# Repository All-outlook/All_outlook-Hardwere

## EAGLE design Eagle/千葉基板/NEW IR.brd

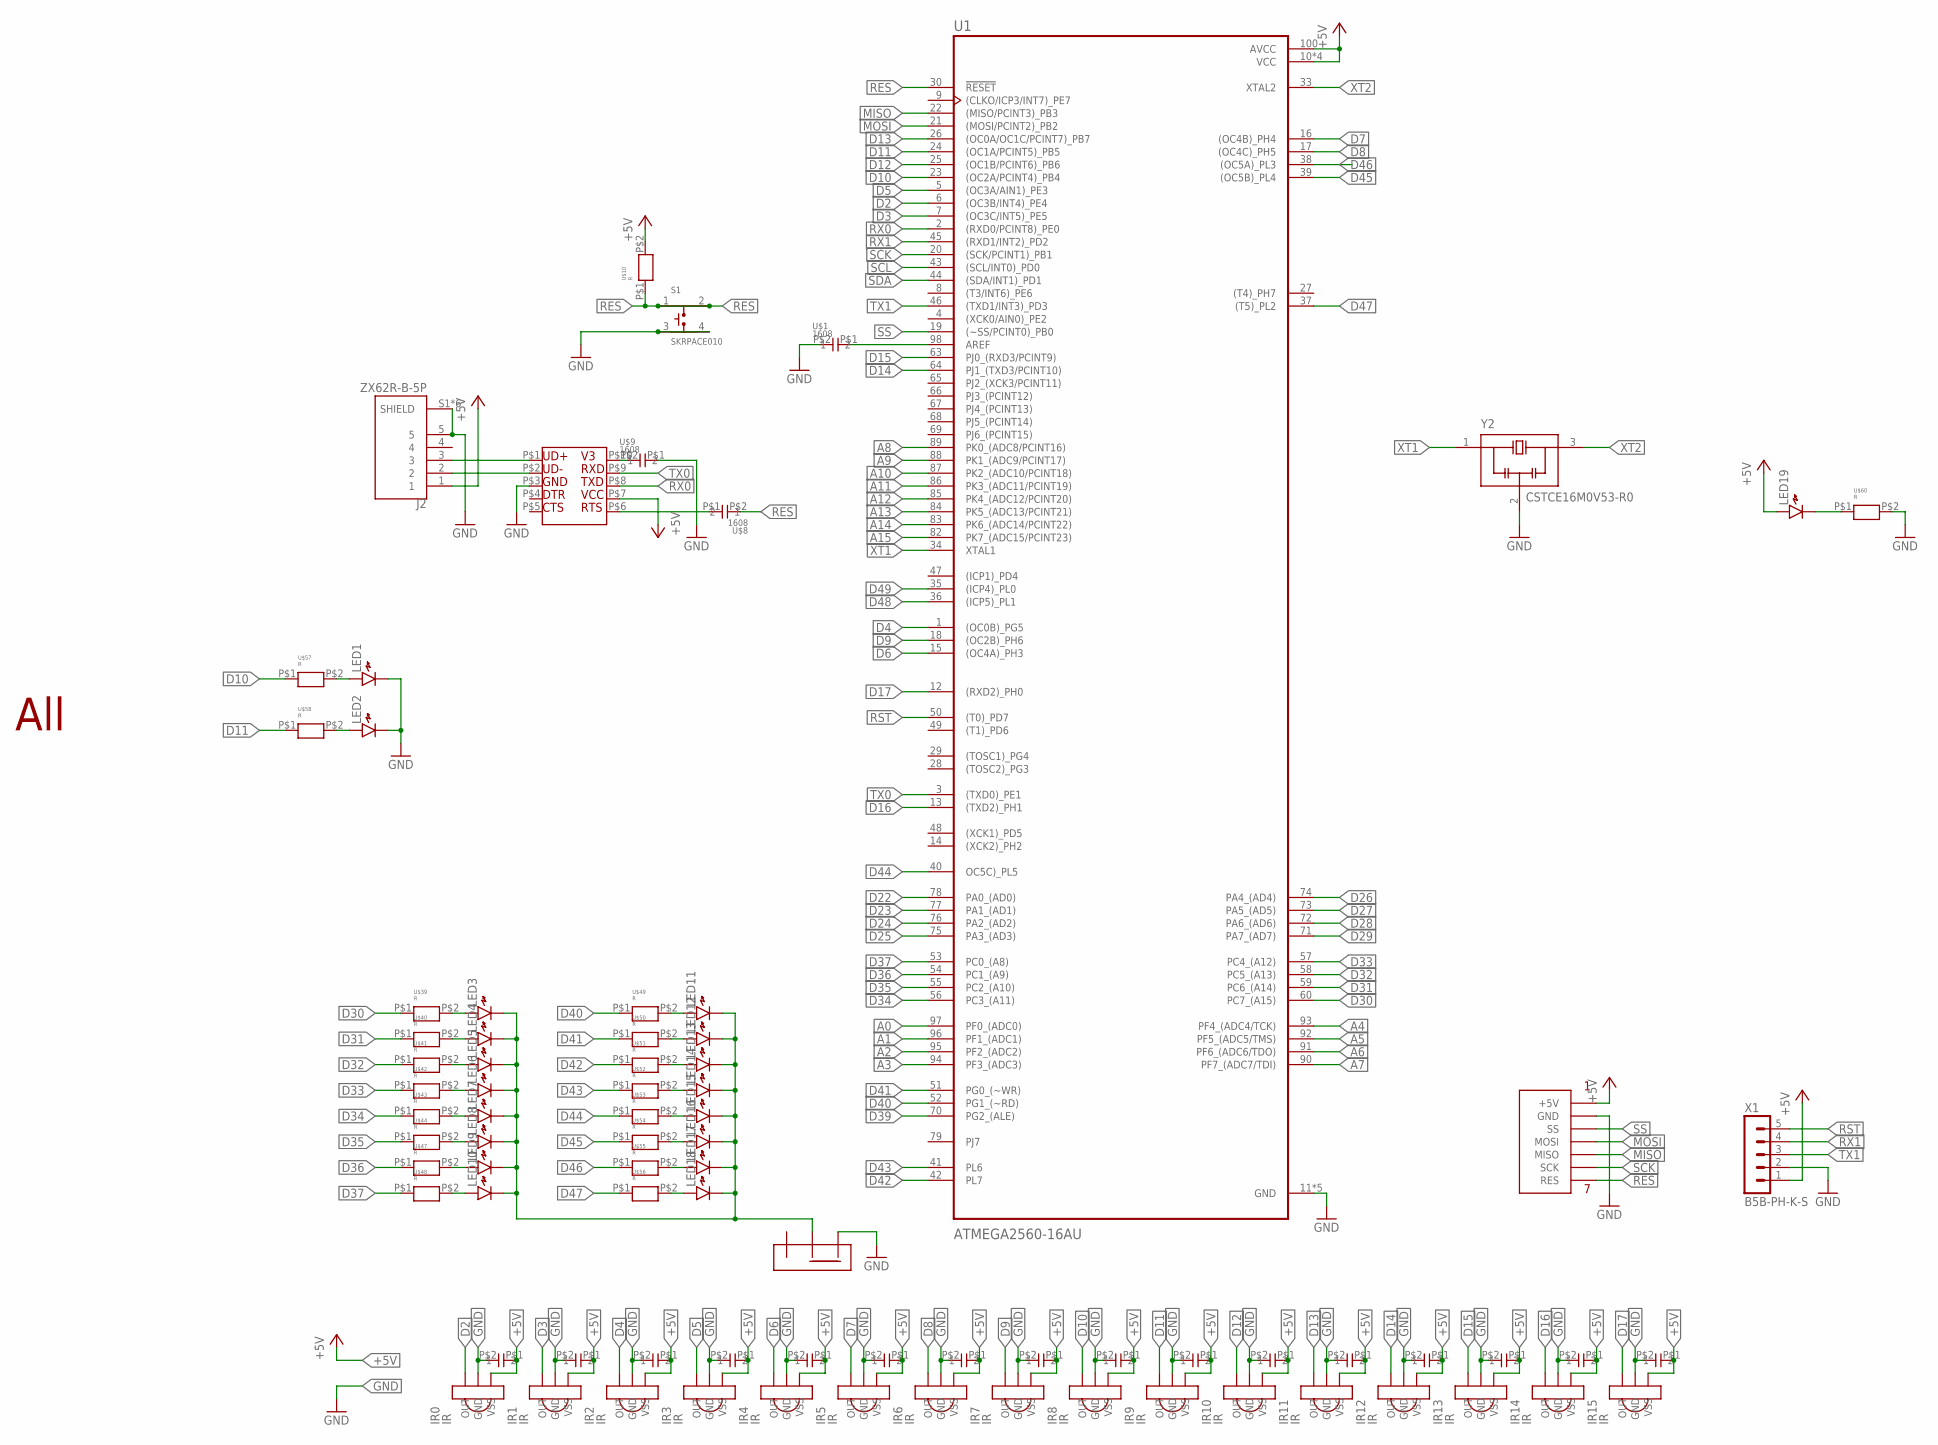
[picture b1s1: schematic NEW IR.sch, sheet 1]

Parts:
IR0, IR1, IR2, IR3, IR4, IR5, IR6, IR7, IR8, IR9, IR10, IR11, IR12, IR13, IR14, IR15: IR
J2: ZX62R-B-5P; HRS_ZX62R-B-5P
LED1, LED2, LED3, LED4, LED5, LED6, LED7, LED8, LED9, LED10, LED11, LED12, LED13, LED14, LED15, LED16, LED17, LED18, LED19: LED1608
S1: SKRPACE010; SW_SKRPACE010
U1: ATMEGA2560-16AU; QFP50P1600X1600X120-100N
U$1, U$2, U$4, U$6, U$8, U$9, U$14, U$16, U$18, U$20, U$22, U$24, U$26, U$28, U$30, U$32, U$34, U$36, U$38: 1608; CON
U$3: ALL
U$5: SSW
U$7: CH340K
U$10, U$39, U$40, U$41, U$42, U$43, U$44, U$47, U$48, U$49, U$50, U$51, U$52, U$53, U$54, U$55, U$56, U$57, U$58, U$60: R; 1608
U$59: SPI
X1: B5B-PH-K-S
Y2: CSTCE16M0V53-R0; OSC_CSTCE16M0V53-R0

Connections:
+5V: IR0.P$3 (VSS), IR1.P$3 (VSS), IR2.P$3 (VSS), IR3.P$3 (VSS), IR4.P$3 (VSS), IR5.P$3 (VSS), IR6.P$3 (VSS), IR7.P$3 (VSS), IR8.P$3 (VSS), IR9.P$3 (VSS), IR10.P$3 (VSS), IR11.P$3 (VSS), IR12.P$3 (VSS), IR13.P$3 (VSS), IR14.P$3 (VSS), IR15.P$3 (VSS), J2.1, LED19.A, U1.10 (VCC), U1.31 (VCC), U1.61 (VCC), U1.80 (VCC), U1.100 (AVCC), U$2.P$1 (1), U$4.P$1 (1), U$6.P$1 (1), U$7.P$7, U$10.P$2, U$14.P$1 (1), U$16.P$1 (1), U$18.P$1 (1), U$20.P$1 (1), U$22.P$1 (1), U$24.P$1 (1), U$26.P$1 (1), U$28.P$1 (1), U$30.P$1 (1), U$32.P$1 (1), U$34.P$1 (1), U$36.P$1 (1), U$38.P$1 (1), U$59.P$1 (+5V), X1.1
A0: U1.97 (PF0_(ADC0))
A1: U1.96 (PF1_(ADC1))
A2: U1.95 (PF2_(ADC2))
A3: U1.94 (PF3_(ADC3))
A4: U1.93 (PF4_(ADC4/TCK))
A5: U1.92 (PF5_(ADC5/TMS))
A6: U1.91 (PF6_(ADC6/TDO))
A7: U1.90 (PF7_(ADC7/TDI))
A8: U1.89 (PK0_(ADC8/PCINT16))
A9: U1.88 (PK1_(ADC9/PCINT17))
A10: U1.87 (PK2_(ADC10/PCINT18))
A11: U1.86 (PK3_(ADC11/PCINT19))
A12: U1.85 (PK4_(ADC12/PCINT20))
A13: U1.84 (PK5_(ADC13/PCINT21))
A14: U1.83 (PK6_(ADC14/PCINT22))
A15: U1.82 (PK7_(ADC15/PCINT23))
D2: IR0.P$1 (OUT), U1.6 ((OC3B/INT4)_PE4)
D3: IR1.P$1 (OUT), U1.7 ((OC3C/INT5)_PE5)
D4: IR2.P$1 (OUT), U1.1 ((OC0B)_PG5)
D5: IR3.P$1 (OUT), U1.5 ((OC3A/AIN1)_PE3)
D6: IR4.P$1 (OUT), U1.15 ((OC4A)_PH3)
D7: IR5.P$1 (OUT), U1.16 ((OC4B)_PH4)
D8: IR6.P$1 (OUT), U1.17 ((OC4C)_PH5)
D9: IR7.P$1 (OUT), U1.18 ((OC2B)_PH6)
D10: IR8.P$1 (OUT), U1.23 ((OC2A/PCINT4)_PB4), U$57.P$1
D11: IR9.P$1 (OUT), U1.24 ((OC1A/PCINT5)_PB5), U$58.P$1
D12: IR10.P$1 (OUT), U1.25 ((OC1B/PCINT6)_PB6)
D13: IR11.P$1 (OUT), U1.26 ((OC0A/OC1C/PCINT7)_PB7)
D14: IR12.P$1 (OUT), U1.64 (PJ1_(TXD3/PCINT10))
D15: IR13.P$1 (OUT), U1.63 (PJ0_(RXD3/PCINT9))
D16: IR14.P$1 (OUT), U1.13 ((TXD2)_PH1)
D17: IR15.P$1 (OUT), U1.12 ((RXD2)_PH0)
D22: U1.78 (PA0_(AD0))
D23: U1.77 (PA1_(AD1))
D24: U1.76 (PA2_(AD2))
D25: U1.75 (PA3_(AD3))
D26: U1.74 (PA4_(AD4))
D27: U1.73 (PA5_(AD5))
D28: U1.72 (PA6_(AD6))
D29: U1.71 (PA7_(AD7))
D30: U1.60 (PC7_(A15)), U$39.P$1
D31: U1.59 (PC6_(A14)), U$40.P$1
D32: U1.58 (PC5_(A13)), U$41.P$1
D33: U1.57 (PC4_(A12)), U$42.P$1
D34: U1.56 (PC3_(A11)), U$43.P$1
D35: U1.55 (PC2_(A10)), U$44.P$1
D36: U1.54 (PC1_(A9)), U$47.P$1
D37: U1.53 (PC0_(A8)), U$48.P$1
D39: U1.70 (PG2_(ALE))
D40: U1.52 (PG1_(~RD)), U$49.P$1
D41: U1.51 (PG0_(~WR)), U$50.P$1
D42: U1.42 (PL7), U$51.P$1
D43: U1.41 (PL6), U$52.P$1
D44: U1.40 (OC5C)_PL5), U$53.P$1
D45: U1.39 ((OC5B)_PL4), U$54.P$1
D46: U1.38 ((OC5A)_PL3), U$55.P$1
D47: U1.37 ((T5)_PL2), U$56.P$1
D48: U1.36 ((ICP5)_PL1)
D49: U1.35 ((ICP4)_PL0)
GND: IR0.P$2 (GND), IR1.P$2 (GND), IR2.P$2 (GND), IR3.P$2 (GND), IR4.P$2 (GND), IR5.P$2 (GND), IR6.P$2 (GND), IR7.P$2 (GND), IR8.P$2 (GND), IR9.P$2 (GND), IR10.P$2 (GND), IR11.P$2 (GND), IR12.P$2 (GND), IR13.P$2 (GND), IR14.P$2 (GND), IR15.P$2 (GND), J2.5, J2.S1 (SHIELD), J2.S2 (SHIELD), J2.S3 (SHIELD), J2.S4 (SHIELD), J2.S5 (SHIELD), J2.S6 (SHIELD), LED1.K, LED2.K, S1.3, S1.4, U1.11 (GND), U1.32 (GND), U1.62 (GND), U1.81 (GND), U1.99 (GND), U$1.P$2 (2), U$2.P$2 (2), U$4.P$2 (2), U$5.P$1, U$6.P$2 (2), U$7.P$3, U$9.P$1 (1), U$14.P$2 (2), U$16.P$2 (2), U$18.P$2 (2), U$20.P$2 (2), U$22.P$2 (2), U$24.P$2 (2), U$26.P$2 (2), U$28.P$2 (2), U$30.P$2 (2), U$32.P$2 (2), U$34.P$2 (2), U$36.P$2 (2), U$38.P$2 (2), U$59.P$2 (GND), U$60.P$2, X1.2, Y2.2 (GND)
MISO: U1.22 ((MISO/PCINT3)_PB3), U$59.P$5 (MISO)
MOSI: U1.21 ((MOSI/PCINT2)_PB2), U$59.P$4 (MOSI)
unnamed: LED3.A, U$39.P$2
unnamed: LED4.A, U$40.P$2
unnamed: LED5.A, U$41.P$2
unnamed: LED6.A, U$42.P$2
unnamed: LED7.A, U$43.P$2
unnamed: LED8.A, U$44.P$2
unnamed: LED9.A, U$47.P$2
unnamed: LED2.A, U$58.P$2
unnamed: LED1.A, U$57.P$2
unnamed: LED3.K, LED4.K, LED5.K, LED6.K, LED7.K, LED8.K, LED9.K, LED10.K, LED11.K, LED12.K, LED13.K, LED14.K, LED15.K, LED16.K, LED17.K, LED18.K, U$5.P$3
unnamed: U$7.P$6, U$8.P$1 (1)
unnamed: J2.2, U$7.P$2
unnamed: J2.3, U$7.P$1
unnamed: U$7.P$10, U$9.P$2 (2)
unnamed: LED10.A, U$48.P$2
unnamed: LED11.A, U$49.P$2
unnamed: LED12.A, U$50.P$2
unnamed: LED13.A, U$51.P$2
unnamed: LED14.A, U$52.P$2
unnamed: LED15.A, U$53.P$2
unnamed: LED16.A, U$54.P$2
unnamed: LED17.A, U$55.P$2
unnamed: LED18.A, U$56.P$2
unnamed: LED19.K, U$60.P$1
unnamed: U1.98 (AREF), U$1.P$1 (1)
RES: S1.1, S1.2, U1.30 (!RESET), U$8.P$2 (2), U$10.P$1, U$59.P$7 (RES)
RST: U1.50 ((T0)_PD7), X1.5
RX0: U1.2 ((RXD0/PCINT8)_PE0), U$7.P$8
RX1: U1.45 ((RXD1/INT2)_PD2), X1.4
SCK: U1.20 ((SCK/PCINT1)_PB1), U$59.P$6 (SCK)
SCL: U1.43 ((SCL/INT0)_PD0)
SDA: U1.44 ((SDA/INT1)_PD1)
SS: U1.19 ((~SS/PCINT0)_PB0), U$59.P$3 (SS)
TX0: U1.3 ((TXD0)_PE1), U$7.P$9
TX1: U1.46 ((TXD1/INT3)_PD3), X1.3
XT1: U1.34 (XTAL1), Y2.1 (IN)
XT2: U1.33 (XTAL2), Y2.3 (OUT)

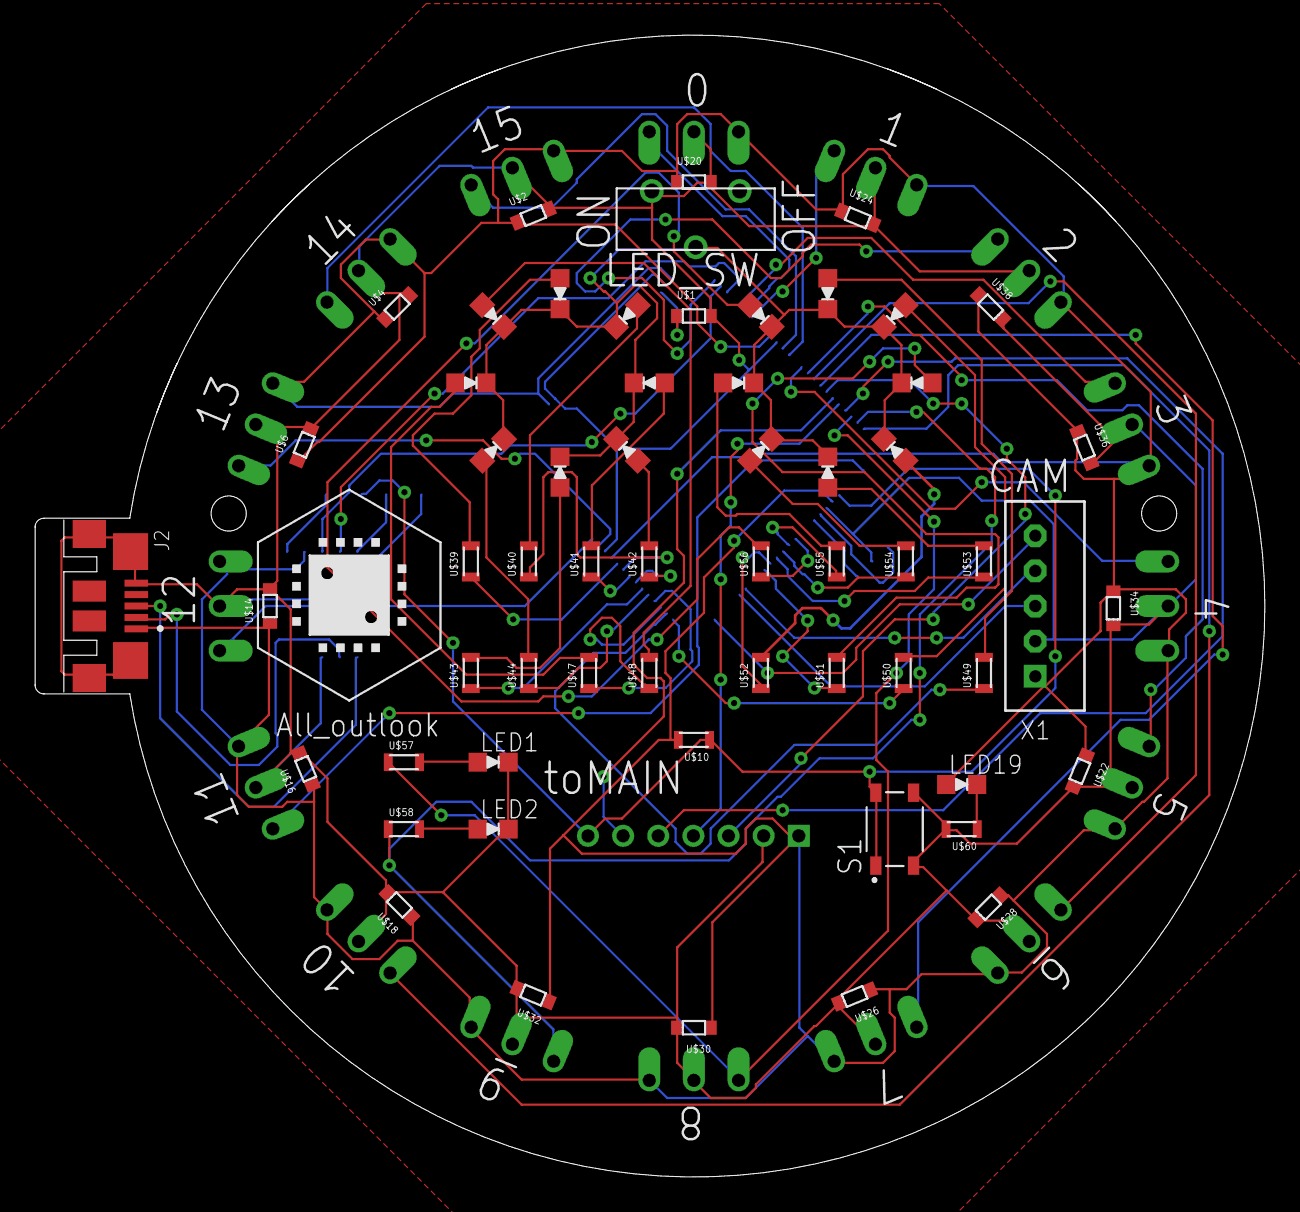
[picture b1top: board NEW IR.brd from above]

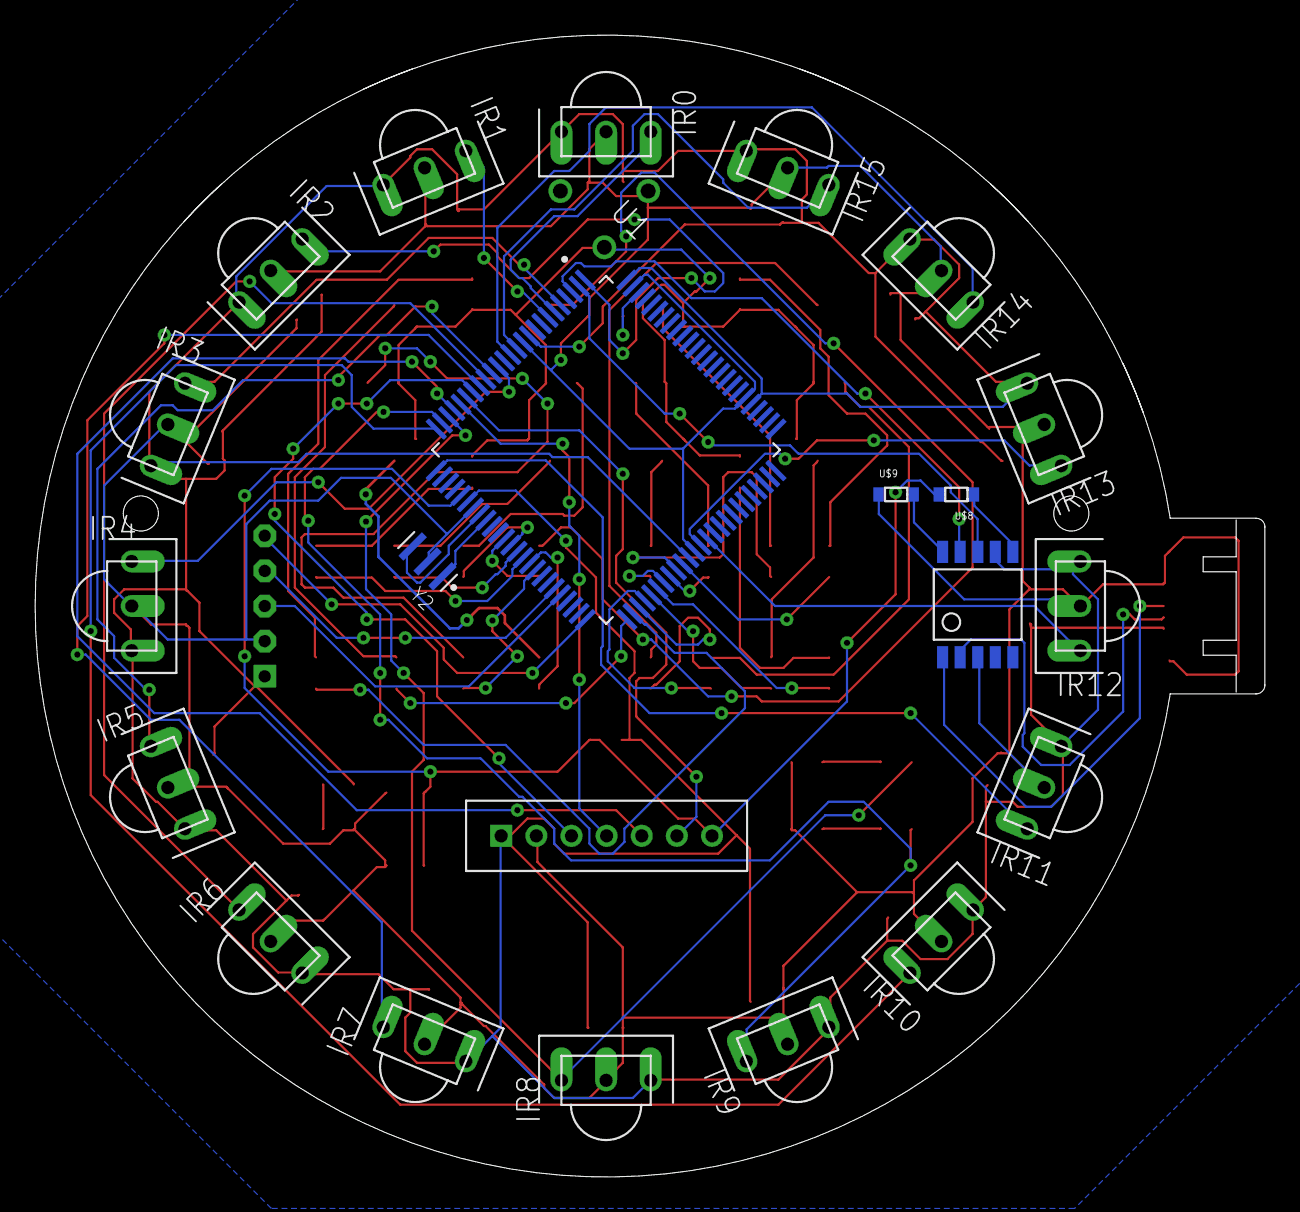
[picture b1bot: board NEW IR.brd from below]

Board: 2 copper layers, 70.0 x 65.0 mm, 83 parts (22 on the bottom side), 71 nets.

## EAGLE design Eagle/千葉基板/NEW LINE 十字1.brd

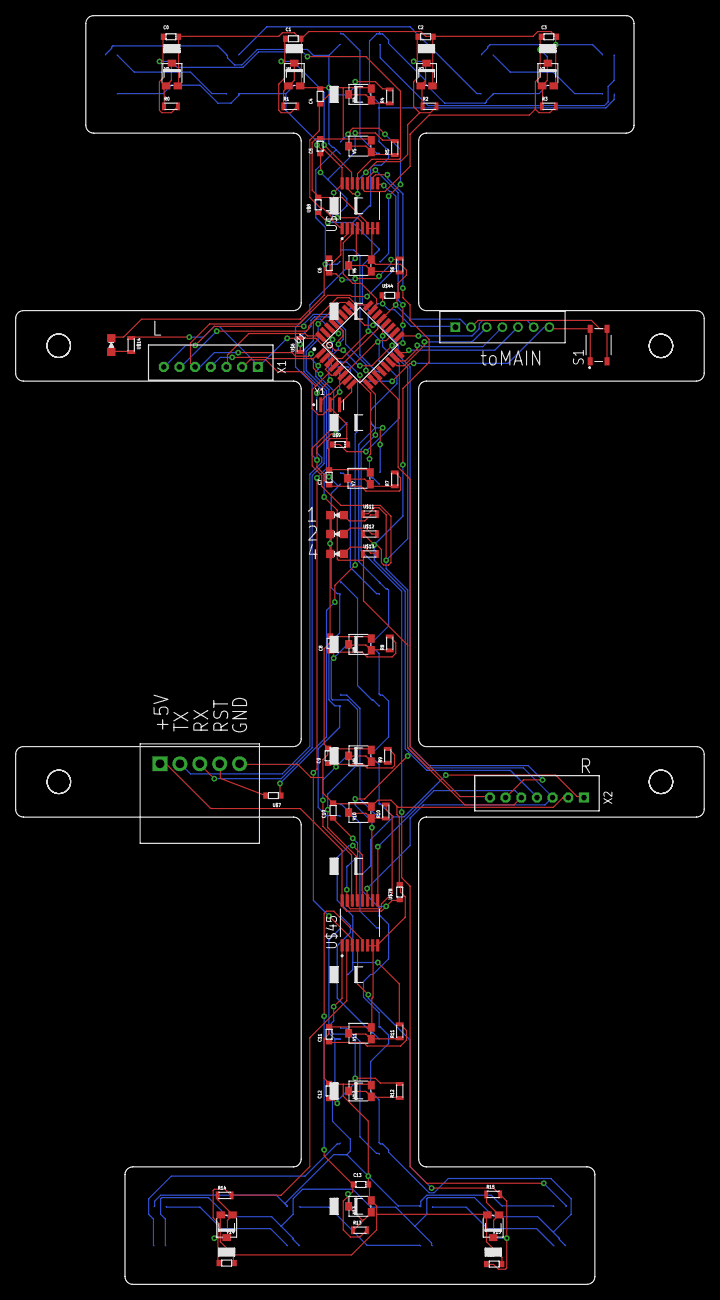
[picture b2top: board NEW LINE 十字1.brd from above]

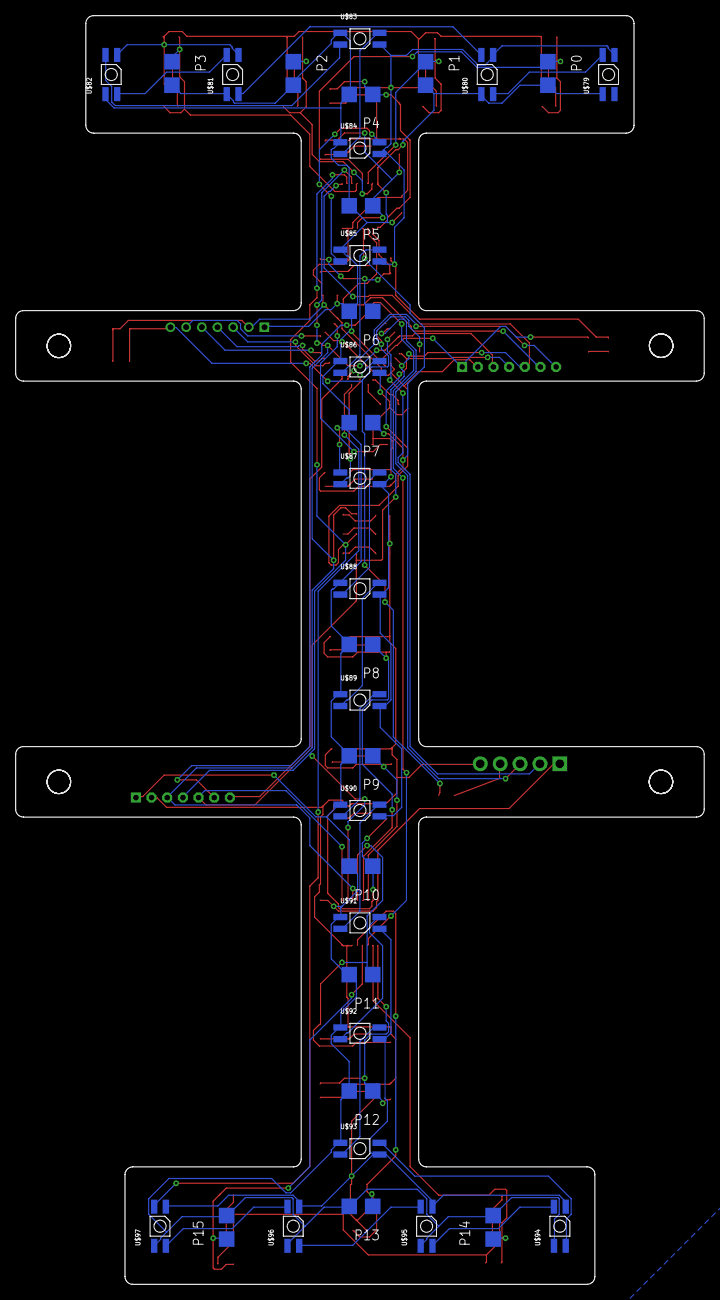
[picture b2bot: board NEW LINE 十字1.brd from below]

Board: 2 copper layers, 87.9 x 162.0 mm, 106 parts (19 on the bottom side), 77 nets.

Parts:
C0, C1, C2, C3, C4, C5, C6, C7, C8, C9, C10, C11, C12, C13, C14, C15: 1608; CON
LED5, LED6, LED7, LED8: LED1608
P0, P1, P2, P3, P4, P5, P6, P7, P8, P9, P10, P11, P12, P13, P14, P15: PHOTO
R0, R1, R2, R3, R4, R5, R6, R7, R8, R9, R10, R11, R12, R13, R14, R15: R; 1608
S1: SKRPACE010; SW_SKRPACE010
U1: ATMEGA328P-AU; QFP80P900X900X120-32N
U$1, U$45: AM; SOP65P640X120-16N
U$6, U$11, U$12, U$13, U$14: R; 1608
U$7, U$8, U$9, U$44, U$78: 1608; CON
U$10: SI
U$15: SPI
U$79, U$80, U$81, U$82, U$83, U$84, U$85, U$86, U$87, U$88, U$89, U$90, U$91, U$92, U$93, U$94, U$95, U$96, U$97: LED
V0, V1, V2, V3, V4, V5, V6, V7, V8, V9, V10, V11, V12, V13, V14, V15: VR
X1, X2: B7B-PH-K-S
Y1: CSTCE16M0V53-R0; OSC_CSTCE16M0V53-R0

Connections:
+5V: P0.P$1, P1.P$1, P2.P$1, P3.P$1, P4.P$1, P5.P$1, P6.P$1, P7.P$1, P8.P$1, P9.P$1, P10.P$1, P11.P$1, P12.P$1, P13.P$1, P14.P$1, P15.P$1, U1.4, U1.6, U1.18, U$1.16, U$6.P$2, U$8.P$1, U$10.P$1, U$14.P$1, U$15.P$1, U$44.P$1, U$45.16, U$78.P$1, U$79.P$1, U$80.P$1, U$81.P$1, U$82.P$1, U$83.P$1, U$84.P$1, U$85.P$1, U$86.P$1, U$87.P$1, U$88.P$1, U$89.P$1, U$90.P$1, U$91.P$1, U$92.P$1, U$93.P$1, U$94.P$1, U$95.P$1, U$96.P$1, U$97.P$1, X1.1, X2.1
A0: U1.23, U$1.3
A1: U1.24, X1.6
A2: U1.25, U$45.3
A3: U1.26, X2.6
CH0: C0.P$1, P0.P$2, R0.P$2, U$1.13
CH1: C1.P$1, P1.P$2, R1.P$2, U$1.14
CH2: C2.P$1, P2.P$2, R2.P$2, U$1.15
CH3: C3.P$1, P3.P$2, R3.P$2, U$1.12
CH4: C4.P$1, P4.P$2, R4.P$2, U$1.1
CH5: C5.P$1, P5.P$2, R5.P$2, U$1.5
CH6: C6.P$1, P6.P$2, R6.P$2, U$1.2
CH7: C7.P$1, P7.P$2, R7.P$2, U$1.4
CH8: C8.P$1, P8.P$2, R8.P$2, U$45.13
CH9: C9.P$1, P9.P$2, R9.P$2, U$45.14
CH10: C10.P$1, P10.P$2, R10.P$2, U$45.15
CH11: C11.P$1, P11.P$2, R11.P$2, U$45.12
CH12: C12.P$1, P12.P$2, R12.P$2, U$45.1
CH13: C13.P$1, P13.P$2, R13.P$2, U$45.5
CH14: C14.P$1, P14.P$2, R14.P$2, U$45.2
CH15: C15.P$1, P15.P$2, R15.P$2, U$45.4
D2: U1.32, U$1.11, U$11.P$1, U$45.11, X1.3, X2.3
D3: U1.1, U$1.10, U$12.P$1, U$45.10, X1.4, X2.4
D4: U1.2, U$1.9, U$13.P$1, U$45.9, X1.5, X2.5
D5: U1.9, U$97.P$4
D6: U1.10, X1.7
D7: U1.11, X2.7
GND: C0.P$2, C1.P$2, C2.P$2, C3.P$2, C4.P$2, C5.P$2, C6.P$2, C7.P$2, C8.P$2, C9.P$2, C10.P$2, C11.P$2, C12.P$2, C13.P$2, C14.P$2, C15.P$2, LED5.K, LED6.K, LED7.K, LED8.K, S1.3, S1.4, U1.3, U1.5, U1.21, U$1.6, U$1.7, U$1.8, U$8.P$2, U$9.P$2, U$10.P$5, U$15.P$2, U$44.P$2, U$45.6, U$45.7, U$45.8, U$78.P$2, U$79.P$3, U$80.P$3, U$81.P$3, U$82.P$3, U$83.P$3, U$84.P$3, U$85.P$3, U$86.P$3, U$87.P$3, U$88.P$3, U$89.P$3, U$90.P$3, U$91.P$3, U$92.P$3, U$93.P$3, U$94.P$3, U$95.P$3, U$96.P$3, U$97.P$3, V0.P$3, V1.P$3, V2.P$3, V3.P$3, V4.P$3, V5.P$3, V6.P$3, V7.P$3, V8.P$3, V9.P$3, V10.P$3, V11.P$3, V12.P$3, V13.P$3, V14.P$3, V15.P$3, X1.2, X2.2, Y1.2
MISO: U1.16, U$15.P$5
MOSI: U1.15, U$15.P$4
unnamed: R0.P$1, V0.P$1, V0.P$2
unnamed: R1.P$1, V1.P$1, V1.P$2
unnamed: R2.P$1, V2.P$1, V2.P$2
unnamed: U1.20, U$9.P$1
unnamed: U$7.P$2, U$10.P$4
unnamed: U1.31, U$10.P$2
unnamed: U1.30, U$10.P$3
unnamed: U1.7, Y1.1
unnamed: U1.8, Y1.3
unnamed: LED7.A, U$13.P$2
unnamed: LED6.A, U$12.P$2
unnamed: LED5.A, U$11.P$2
unnamed: LED8.A, U$14.P$2
unnamed: R3.P$1, V3.P$1, V3.P$2
unnamed: R4.P$1, V4.P$1, V4.P$2
unnamed: R5.P$1, V5.P$1, V5.P$2
unnamed: R6.P$1, V6.P$1, V6.P$2
unnamed: R7.P$1, V7.P$1, V7.P$2
unnamed: R8.P$1, V8.P$1, V8.P$2
unnamed: R9.P$1, V9.P$1, V9.P$2
unnamed: R10.P$1, V10.P$1, V10.P$2
unnamed: R11.P$1, V11.P$1, V11.P$2
unnamed: R12.P$1, V12.P$1, V12.P$2
unnamed: R13.P$1, V13.P$1, V13.P$2
unnamed: R14.P$1, V14.P$1, V14.P$2
unnamed: R15.P$1, V15.P$1, V15.P$2
unnamed: U$79.P$4, U$80.P$2
unnamed: U$80.P$4, U$81.P$2
unnamed: U$81.P$4, U$82.P$2
unnamed: U$82.P$4, U$83.P$2
unnamed: U$83.P$4, U$84.P$2
unnamed: U$84.P$4, U$85.P$2
unnamed: U$85.P$4, U$86.P$2
unnamed: U$86.P$4, U$87.P$2
unnamed: U$87.P$4, U$88.P$2
unnamed: U$88.P$4, U$89.P$2
unnamed: U$89.P$4, U$90.P$2
unnamed: U$90.P$4, U$91.P$2
unnamed: U$91.P$4, U$92.P$2
unnamed: U$92.P$4, U$93.P$2
unnamed: U$93.P$4, U$94.P$2
unnamed: U$94.P$4, U$95.P$2
unnamed: U$95.P$4, U$96.P$2
unnamed: U$96.P$4, U$97.P$2
RES: S1.1, S1.2, U1.29, U$6.P$1, U$7.P$1, U$15.P$7
SCK: U1.17, U$15.P$6
SS: U1.14, U$15.P$3

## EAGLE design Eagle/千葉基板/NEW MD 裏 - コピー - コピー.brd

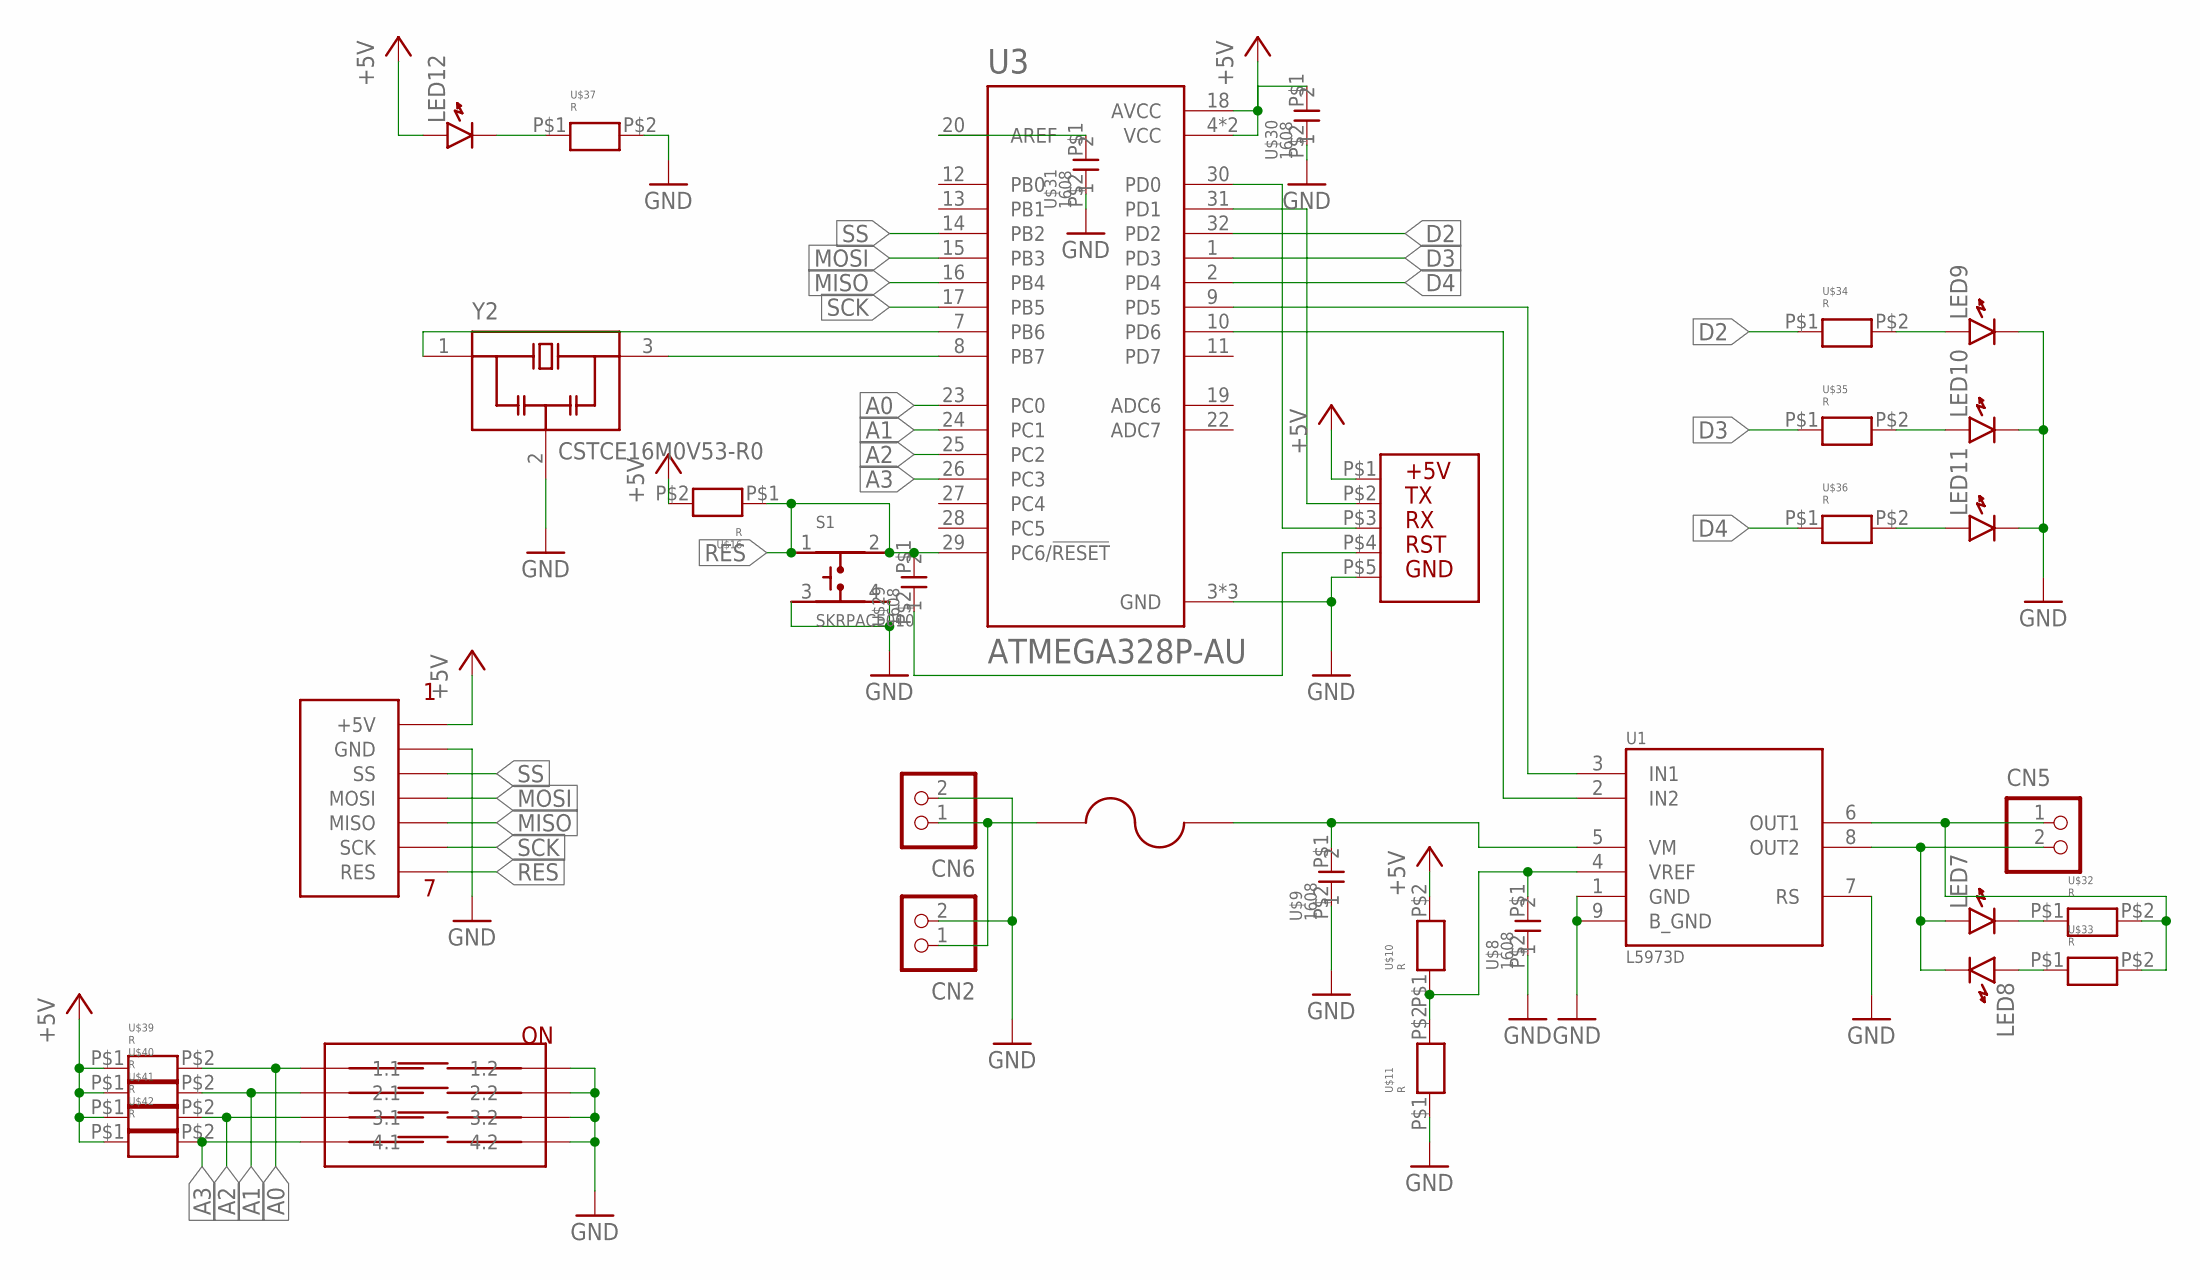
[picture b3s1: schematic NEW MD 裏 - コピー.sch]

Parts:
CN2, CN6: B2B-XH-A
CN5: S2B-XH-A
LED7, LED8, LED9, LED10, LED11, LED12: LED1608
S1: SKRPACE010; SW_SKRPACE010
U1: L5973D; SOIC127P600X170-9N
U3: ATMEGA328P-AU; QFP80P900X900X120-32N
U$1: FUSE3.7A
U$8, U$9, U$29, U$30, U$31: 1608; CON
U$10, U$11, U$16, U$32, U$33, U$34, U$35, U$36, U$37, U$39, U$40, U$41, U$42: R; 1608
U$38: 4P
U$43: SPI
U$44: SI
Y2: CSTCE16M0V53-R0; OSC_CSTCE16M0V53-R0

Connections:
+5V: LED12.A, U3.4 (VCC), U3.6 (VCC), U3.18 (AVCC), U$10.P$2, U$16.P$2, U$30.P$1 (1), U$39.P$1, U$40.P$1, U$41.P$1, U$42.P$1, U$43.P$1 (+5V), U$44.P$1
A0: U3.23 (PC0), U$38.1.1, U$39.P$2
A1: U3.24 (PC1), U$38.2.1, U$40.P$2
A2: U3.25 (PC2), U$38.3.1, U$41.P$2
A3: U3.26 (PC3), U$38.4.1, U$42.P$2
D2: U3.32 (PD2), U$34.P$1
D3: U3.1 (PD3), U$35.P$1
D4: U3.2 (PD4), U$36.P$1
GND: CN2.2, CN6.2, LED9.K, LED10.K, LED11.K, S1.3, S1.4, U1.1 (GND), U1.7 (RS), U1.9 (B_GND), U3.3 (GND), U3.5 (GND), U3.21 (GND), U$8.P$2 (2), U$9.P$2 (2), U$11.P$1, U$30.P$2 (2), U$31.P$2 (2), U$37.P$2, U$38.1.2, U$38.2.2, U$38.3.2, U$38.4.2, U$43.P$2 (GND), U$44.P$5, Y2.2 (GND)
MISO: U3.16 (PB4), U$43.P$5 (MISO)
MOSI: U3.15 (PB3), U$43.P$4 (MOSI)
unnamed: U1.5 (VM), U$1.P$2, U$9.P$1 (1)
unnamed: U1.4 (VREF), U$8.P$1 (1), U$10.P$1, U$11.P$2
unnamed: U3.20 (AREF), U$31.P$1 (1)
unnamed: U$29.P$2 (2), U$44.P$4
unnamed: U3.31 (PD1), U$44.P$2
unnamed: U3.30 (PD0), U$44.P$3
unnamed: CN2.1, CN6.1, U$1.P$1
unnamed: CN5.2, LED7.A, LED8.K, U1.8 (OUT2)
unnamed: CN5.1, U1.6 (OUT1), U$32.P$2, U$33.P$2
unnamed: U1.2 (IN2), U3.10 (PD6)
unnamed: U1.3 (IN1), U3.9 (PD5)
unnamed: U3.7 (PB6), Y2.1 (IN)
unnamed: U3.8 (PB7), Y2.3 (OUT)
unnamed: LED8.A, U$33.P$1
unnamed: LED7.K, U$32.P$1
unnamed: LED10.A, U$35.P$2
unnamed: LED9.A, U$34.P$2
unnamed: LED11.A, U$36.P$2
unnamed: LED12.K, U$37.P$1
RES: S1.1, S1.2, U3.29 (PC6/!RESET), U$16.P$1, U$29.P$1 (1), U$43.P$7 (RES)
SCK: U3.17 (PB5), U$43.P$6 (SCK)
SS: U3.14 (PB2), U$43.P$3 (SS)

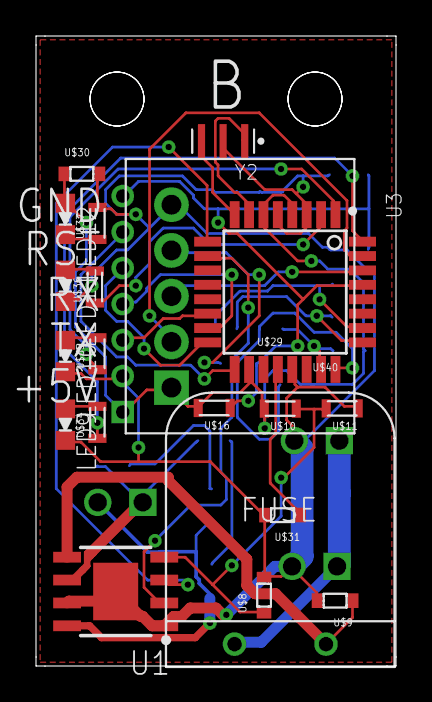
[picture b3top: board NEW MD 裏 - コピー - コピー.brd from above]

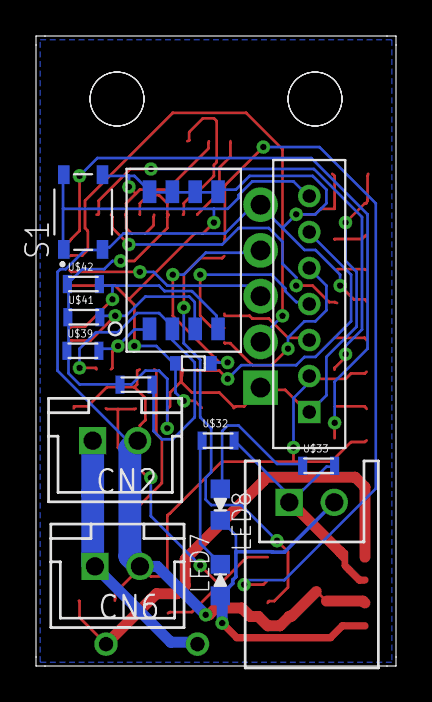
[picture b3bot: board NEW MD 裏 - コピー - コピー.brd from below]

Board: 2 copper layers, 20.0 x 35.0 mm, 35 parts (15 on the bottom side), 33 nets.

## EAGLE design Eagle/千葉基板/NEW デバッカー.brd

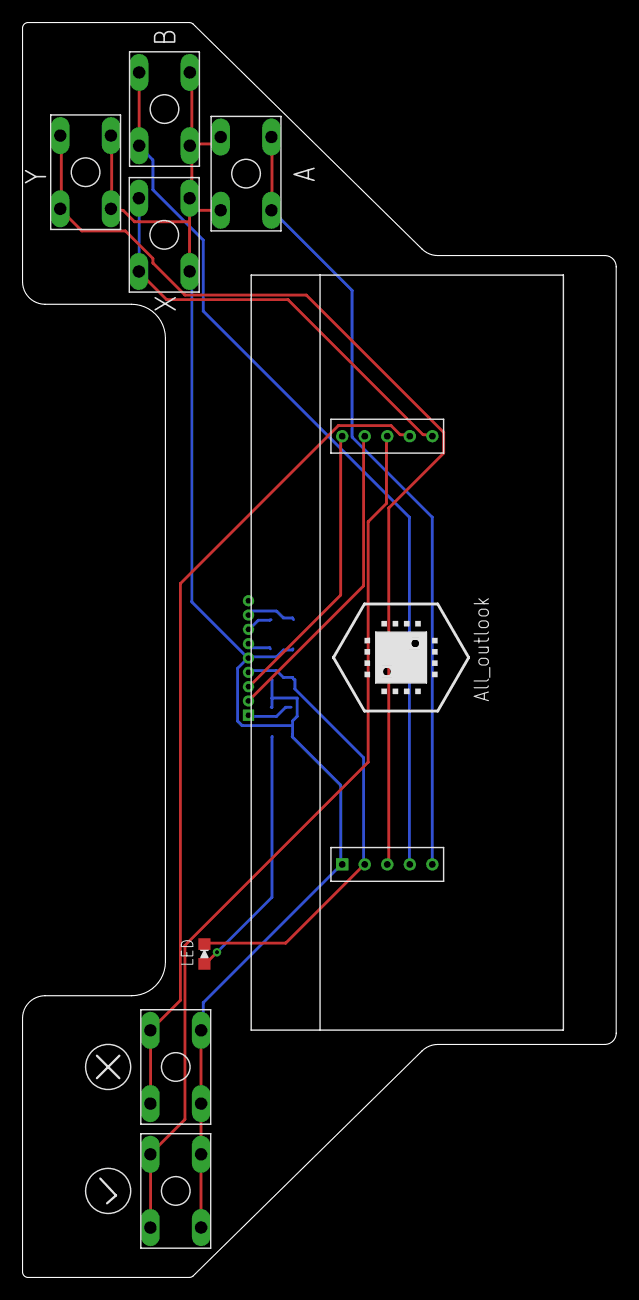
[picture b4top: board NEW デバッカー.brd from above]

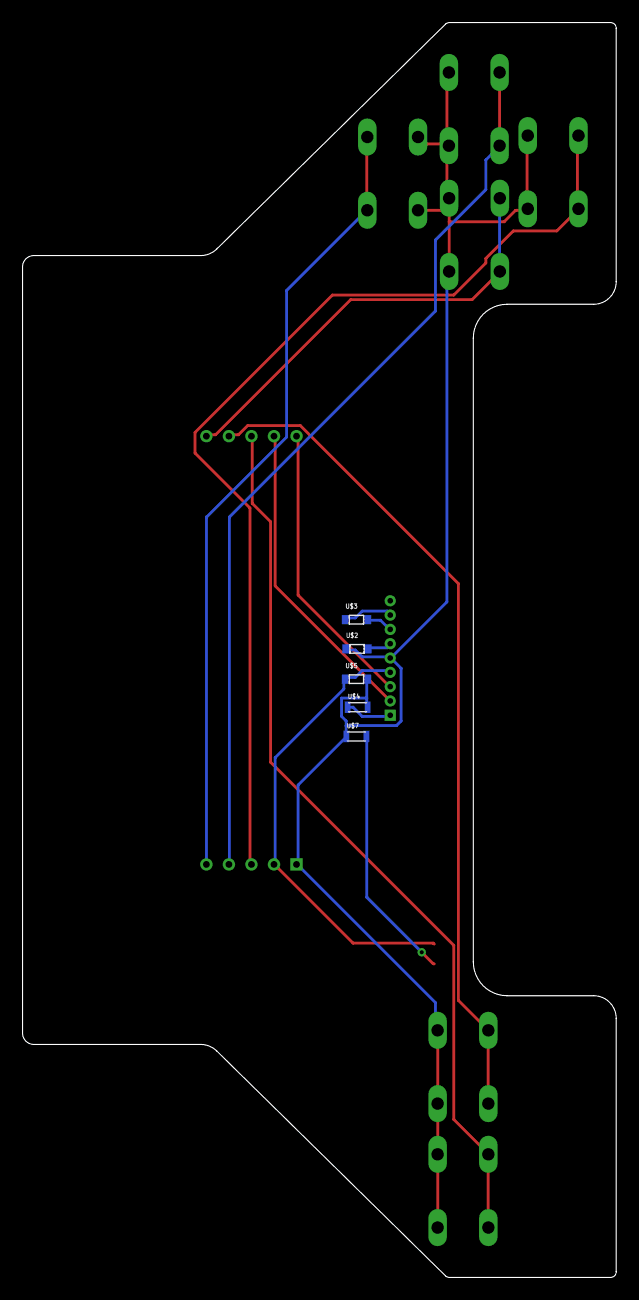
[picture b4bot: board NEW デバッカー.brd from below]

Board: 2 copper layers, 52.7 x 111.4 mm, 15 parts (5 on the bottom side), 15 nets.

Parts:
LED: LED1608
U$1: LIQUIDCRYSTAL
U$2, U$3, U$5: 1608; CON
U$4, U$7: R; 1608
U$6, U$10, U$11, U$12, U$13, U$14: TAKUTO6MM
U$8: UI
U$9: ALL

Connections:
+5V: U$1.P$5, U$2.P$1, U$4.P$2, U$5.P$2, U$6.P$3, U$6.P$4, U$7.P$1, U$8.P$1, U$10.P$3, U$10.P$4, U$11.P$3, U$11.P$4, U$12.P$3, U$12.P$4, U$13.P$3, U$13.P$4, U$14.P$3, U$14.P$4
GND: LED.K, U$1.P$4, U$5.P$1, U$8.P$2
unnamed: LED.A, U$7.P$2
unnamed: U$1.P$7, U$3.P$2
unnamed: U$1.P$8, U$3.P$1
unnamed: U$1.P$6, U$2.P$2
unnamed: U$1.P$1, U$4.P$1
S1: U$6.P$1, U$6.P$2, U$8.P$3
S2: U$8.P$4, U$10.P$1, U$10.P$2
S3: U$8.P$5, U$11.P$1, U$11.P$2
S4: U$8.P$6, U$12.P$1, U$12.P$2
S5: U$8.P$7, U$13.P$1, U$13.P$2
S6: U$8.P$8, U$14.P$1, U$14.P$2
SCL: U$1.P$2, U$8.P$9
SDA: U$1.P$3, U$8.P$10

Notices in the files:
parts and their libraries:
lm1117: (c) 2014 Samuel Lourenço
